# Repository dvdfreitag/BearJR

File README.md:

# BearJR

Move along... nothing to see here. Yet.

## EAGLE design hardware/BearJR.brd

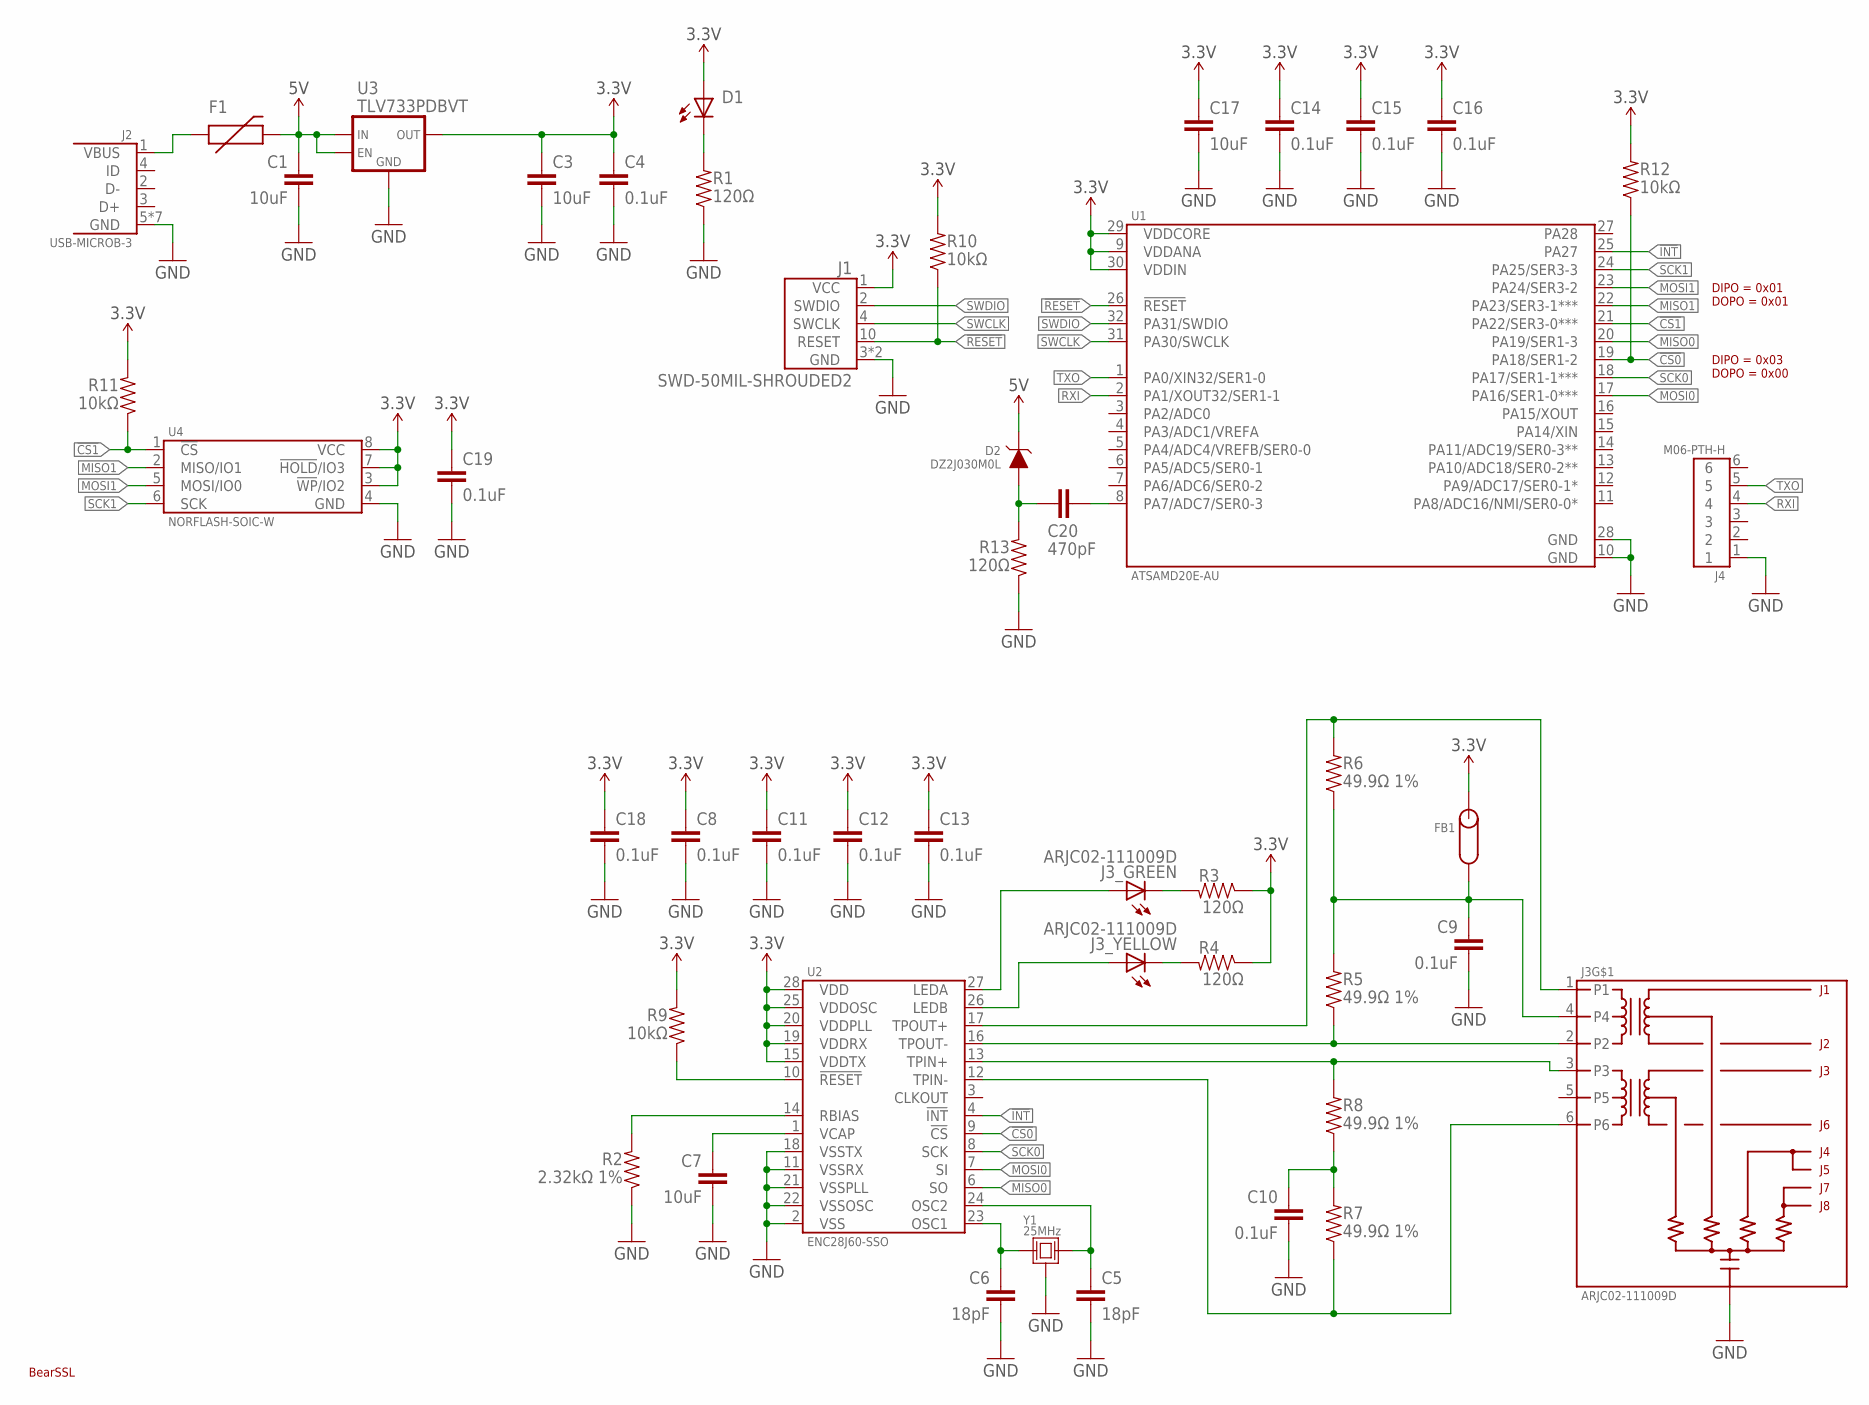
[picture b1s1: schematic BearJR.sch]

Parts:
C1, C3, C7, C17: 10uF; 0603-CAP
C4, C8, C9, C10, C11, C12, C13, C14, C15, C16, C18, C19: 0.1uF; 0603-CAP
C5, C6: 18pF; 0603-CAP
C20: 470pF; 0603-CAP
D1: LED-0603; 0603-LED
D2: DZ2J030M0L; SC-90
F1: PTC-1206; 1206-PTC
FB1: FERRITE-0805; 0805
J1: SWD-50MIL-SHROUDED2; M05X2-50MIL-SHROUD
J2: USB-MICROB-3; 10118192-0001LF
J3: ARJC02-111009D; ETHERNET
J4: M06-PTH-H
R1, R3, R4, R13: 120Ω; 0603-CAP
R2: 2.32kΩ 1%; 0603-CAP
R5, R6, R7, R8: 49.9Ω 1%; 0805-RES
R9, R10, R11, R12: 10kΩ; 0603-CAP
U1: ATSAMD20E-AU; TQFP-32
U2: ENC28J60-SSO; SSOP-28
U3: TLV733PDBVT; SOT-23-5
U4: NORFLASH-SOIC-W; SOIC-8-W
U$1: BEAR_SSL
Y1: 25MHz; FA-238

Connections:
3.3V: C3.1, C4.1, C8.1, C11.1, C12.1, C13.1, C14.1, C15.1, C16.1, C17.1, C18.1, C19.1, D1.A, FB1.2, J1.1 (VCC), R3.1, R4.1, R9.2, R10.2, R11.2, R12.2, U1.9 (VDDANA), U1.29 (VDDCORE), U1.30 (VDDIN), U2.15 (VDDTX), U2.19 (VDDRX), U2.20 (VDDPLL), U2.25 (VDDOSC), U2.28 (VDD), U3.5 (OUT), U4.3 (!WP!/IO2), U4.7 (!HOLD!/IO3), U4.8 (VCC)
5V: C1.1, D2.C, F1.P$2 (2), U3.1 (IN), U3.3 (EN)
!CS0: R12.1, U1.19 (PA18/SER1-2), U2.9 (!CS)
!CS1: R11.1, U1.21 (PA22/SER3-0***), U4.1 (!CS)
!INT: U1.25 (PA27), U2.4 (!INT)
!RESET: J1.10 (RESET), R10.1, U1.26 (!RESET)
CT: C9.1, FB1.1, J3.4, R5.2, R6.1
GND: C1.2, C3.2, C4.2, C5.2, C6.2, C7.2, C8.2, C9.2, C10.2, C11.2, C12.2, C13.2, C14.2, C15.2, C16.2, C17.2, C18.2, C19.2, J1.3 (GND), J1.5 (GND), J2.5 (GND), J2.P$6 (GND), J2.P$7 (GND), J2.P$8 (GND), J2.P$9 (GND), J2.P$10 (GND), J2.P$11 (GND), J3.8, J3.P$5 (P8), J3.P$6 (P8), J4.1, R1.1, R2.1, R13.1, U1.10 (GND), U1.28 (GND), U2.2 (VSS), U2.11 (VSSRX), U2.18 (VSSTX), U2.21 (VSSPLL), U2.22 (VSSOSC), U3.2 (GND), U4.4 (GND), Y1.2 (GND), Y1.4 (GND)
MISO0: U1.20 (PA19/SER1-3), U2.6 (SO)
MISO1: U1.22 (PA23/SER3-1***), U4.2 (MISO/IO1)
MOSI0: U1.17 (PA16/SER1-0***), U2.7 (SI)
MOSI1: U1.23 (PA24/SER3-2), U4.5 (MOSI/IO0)
unnamed: F1.P$1 (1), J2.1 (VBUS)
unnamed: R2.2, U2.14 (RBIAS)
unnamed: C7.1, U2.1 (VCAP)
unnamed: D1.C, R1.2
unnamed: C6.1, U2.23 (OSC1), Y1.1
unnamed: C5.1, U2.24 (OSC2), Y1.3 (2)
unnamed: R9.1, U2.10 (!RESET)
unnamed: J3.9 (A), U2.27 (LEDA)
unnamed: J3.11 (A), U2.26 (LEDB)
unnamed: J3.10 (C), R3.2
unnamed: J3.12 (C), R4.2
unnamed: C20.1, D2.A, R13.2
unnamed: C20.2, U1.8 (PA7/ADC7/SER0-3)
unnamed: C10.1, R7.2, R8.1
RXI: J4.4, U1.2 (PA1/XOUT32/SER1-1)
SCK0: U1.18 (PA17/SER1-1***), U2.8 (SCK)
SCK1: U1.24 (PA25/SER3-3), U4.6 (SCK)
SWCLK: J1.4 (SWCLK), U1.31 (PA30/SWCLK)
SWDIO: J1.2 (SWDIO), U1.32 (PA31/SWDIO)
TPIN_N: J3.6, R7.1, U2.12 (TPIN-)
TPIN_P: J3.3, R8.2, U2.13 (TPIN+)
TPOUT_N: J3.2, R5.1, U2.16 (TPOUT-)
TPOUT_P: J3.1, R6.2, U2.17 (TPOUT+)
TXO: J4.5, U1.1 (PA0/XIN32/SER1-0)

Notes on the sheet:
DIPO = 0x01 DOPO = 0x01
DIPO = 0x03 DOPO = 0x00

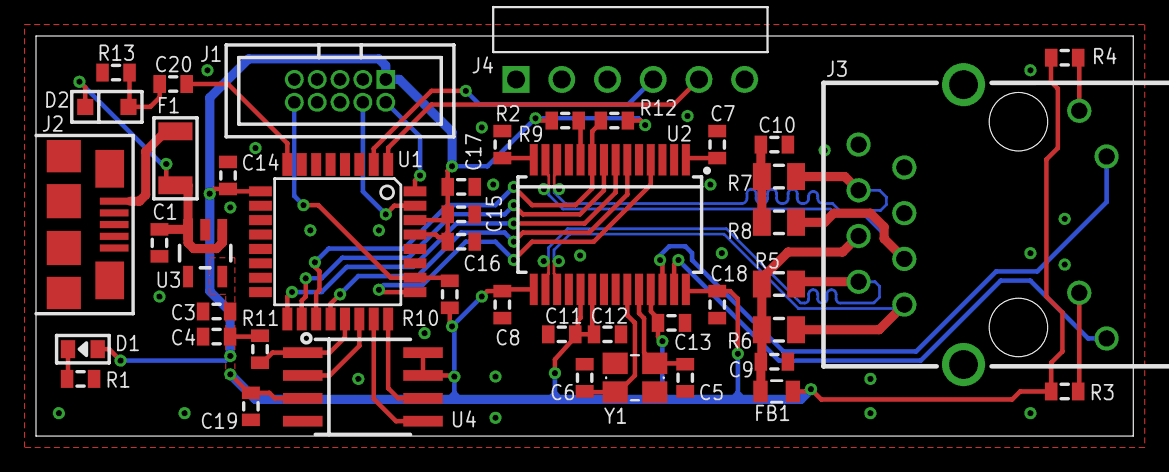
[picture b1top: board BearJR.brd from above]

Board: 2 copper layers, 61.0 x 22.2 mm, 46 parts (1 on the bottom side), 36 nets.

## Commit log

2016-12-26 added examples
2016-12-27 Added a few notes, as well as the board files
2016-12-27 moar notes
2016-12-27 notes
2016-12-29 More notes, some formatting changes
2016-12-30 Updated blink example, also remove the bitmasks
2016-12-31 Fix blink example
    Add working blink code
2016-12-31 Add OpenOCD target
    Fix an issue with handlers, and add a programming target for OpenOCD
2017-01-01 Add EXTINT example
2017-01-01 Update library
    More library changes, remove all bitmasks
2017-01-03 Add usart example
2017-01-04 Add benchmark code
2017-01-05 Add benchmark arguments
2017-01-09 Add SPI example
2017-01-10 Add some peripheral drivers
2017-01-12 Add adc driver
2017-01-13 Start ENC28J60 driver
2017-01-16 Add ENC28J60 driver
2017-05-20 Add External Interrupt driver for ethernet interrupts
2017-05-23 Add working code
